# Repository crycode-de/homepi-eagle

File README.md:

# HomePi Eagle

Dieses Repository beinhaltet die Eagle-Dateien für die Hardware des HomePi Projektes.

Das gesamte HomePi Projekt wird hier beschrieben: [https://crycode.de/category/homepi](https://crycode.de/category/homepi)

**Die Verwendung erfolgt grundsätzlich auf eigenes Risiko und ohne Gewähr!**

## Lizenz

Creative Commons Attribution-NonCommercial-ShareAlike 4.0 International (CC BY-NC-SA 4.0)

Copyright (c) 2015-2024 Peter Müller <peter@crycode.de> [https://crycode.de/](https://crycode.de/)

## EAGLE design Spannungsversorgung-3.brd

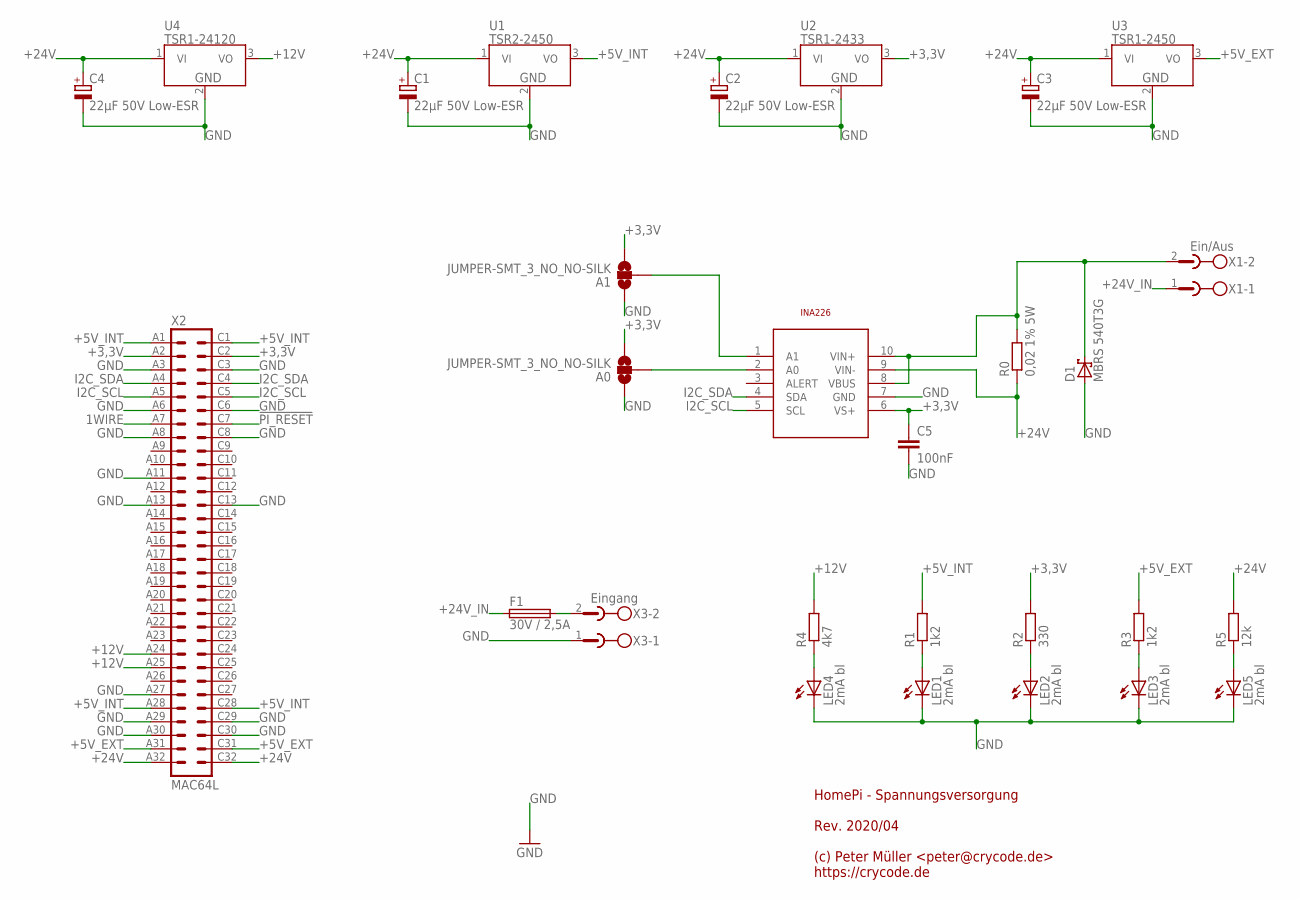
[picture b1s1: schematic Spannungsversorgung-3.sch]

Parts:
A0, A1: JUMPER-SMT_3_NO_NO-SILK; SMT-JUMPER_3_NO_NO-SILK
C1, C2, C3, C4: 22µF 50V Low-ESR; E2-5
C5: 100nF; C1206
D1: MBRS 540T3G; SMC
F1: 30V / 2,5A; LITTLEFUSE
IC1: TI-INA226
LED1, LED2, LED3, LED4, LED5: 2mA bl; CHIPLED_1206
R0: 0,02 1% 5W; R2512
R1, R3: 1k2; R1206
R2: 330; R1206
R4: 4k7; R1206
R5: 12k; R1206
U1: TSR2-2450; TSR2
U2: TSR1-2433; TSR1
U3: TSR1-2450; TSR1
U4: TSR1-24120; TSR1
X1: Ein/Aus; MSTBA2
X2: MAC64L
X3: Eingang; MSTBA2

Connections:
1WIRE: X2.A7
!PI_RESET: X2.C7
+3,3V: A0.3, A1.3, C5.1, IC1.6 (VS+), R2.2, U2.3 (VO), X2.A2, X2.C2
+5V_EXT: R3.2, U3.3 (VO), X2.A31, X2.C31
+5V_INT: R1.2, U1.3 (VO), X2.A1, X2.A28, X2.C1, X2.C28
+12V: R4.2, U4.3 (VO), X2.A24, X2.A25
+24V: C1.+, C2.+, C3.+, C4.+, IC1.9 (VIN-), R0.1, R5.2, U1.1 (VI), U2.1 (VI), U3.1 (VI), U4.1 (VI), X2.A32, X2.C32
+24V_1: D1.C, IC1.8 (VBUS), IC1.10 (VIN+), R0.2, X1.2
+24V_IN: F1.1, X1.1
+24V_IN_RAW: F1.2, X3.2
GND: A0.1, A1.1, C1.-, C2.-, C3.-, C4.-, C5.2, D1.A, IC1.7 (GND), LED1.C, LED2.C, LED3.C, LED4.C, LED5.C, U1.2 (GND), U2.2 (GND), U3.2 (GND), U4.2 (GND), X2.A3, X2.A6, X2.A8, X2.A11, X2.A13, X2.A27, X2.A29, X2.A30, X2.C3, X2.C6, X2.C8, X2.C13, X2.C29, X2.C30, X3.1
I2C_SCL: IC1.5 (SCL), X2.A5, X2.C5
I2C_SDA: IC1.4 (SDA), X2.A4, X2.C4
unnamed: A0.2, IC1.2 (A0)
unnamed: A1.2, IC1.1 (A1)
unnamed: LED5.A, R5.1
unnamed: LED1.A, R1.1
unnamed: LED2.A, R2.1
unnamed: LED3.A, R3.1
unnamed: LED4.A, R4.1

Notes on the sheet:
HomePi - Spannungsversorgung Rev. 2020/04 (c) Peter Müller <peter@crycode.de> https://crycode.de

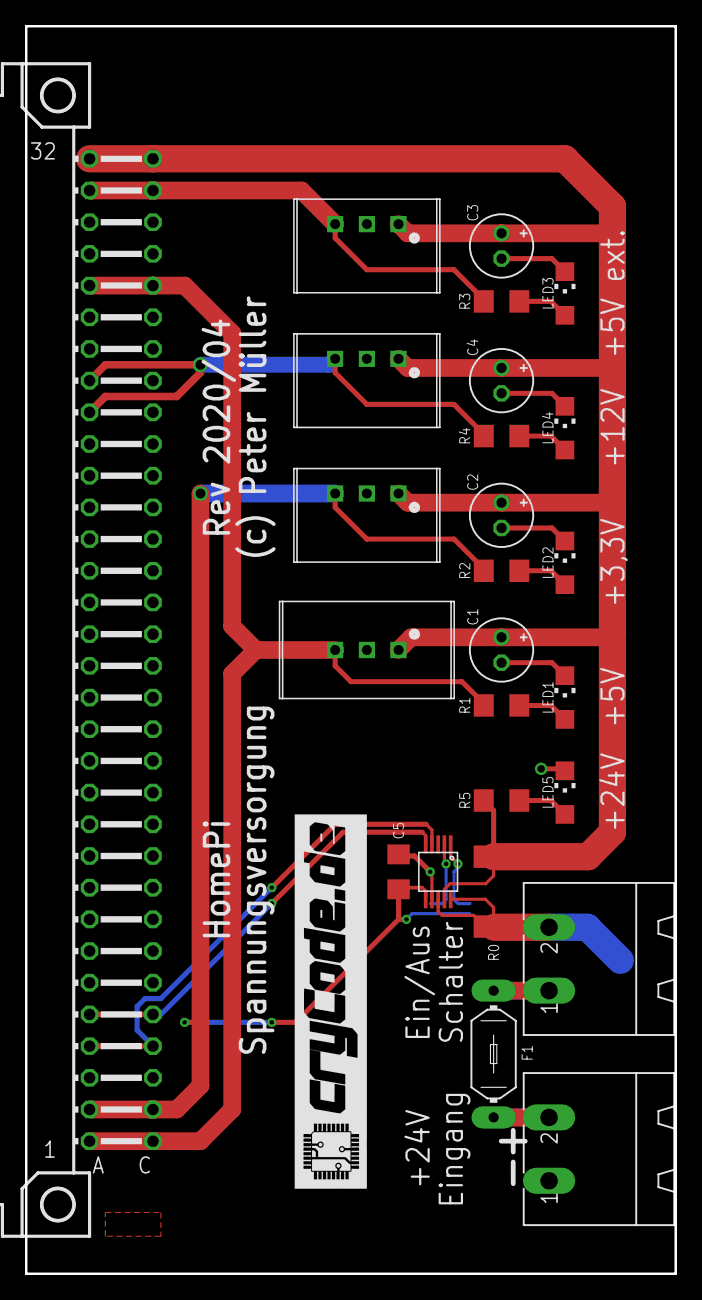
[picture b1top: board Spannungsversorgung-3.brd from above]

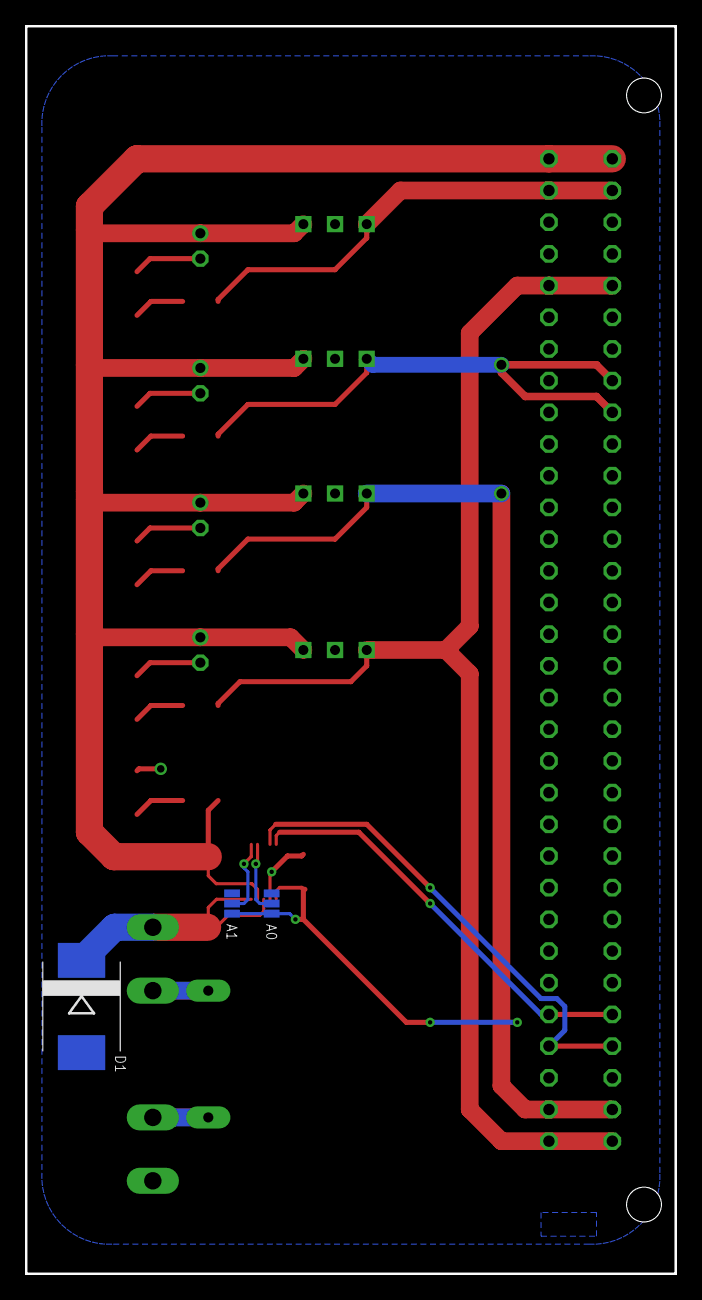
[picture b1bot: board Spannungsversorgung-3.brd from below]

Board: 2 copper layers, 52.1 x 100.0 mm, 29 parts (3 on the bottom side), 18 nets.

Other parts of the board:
U$1: 30MM

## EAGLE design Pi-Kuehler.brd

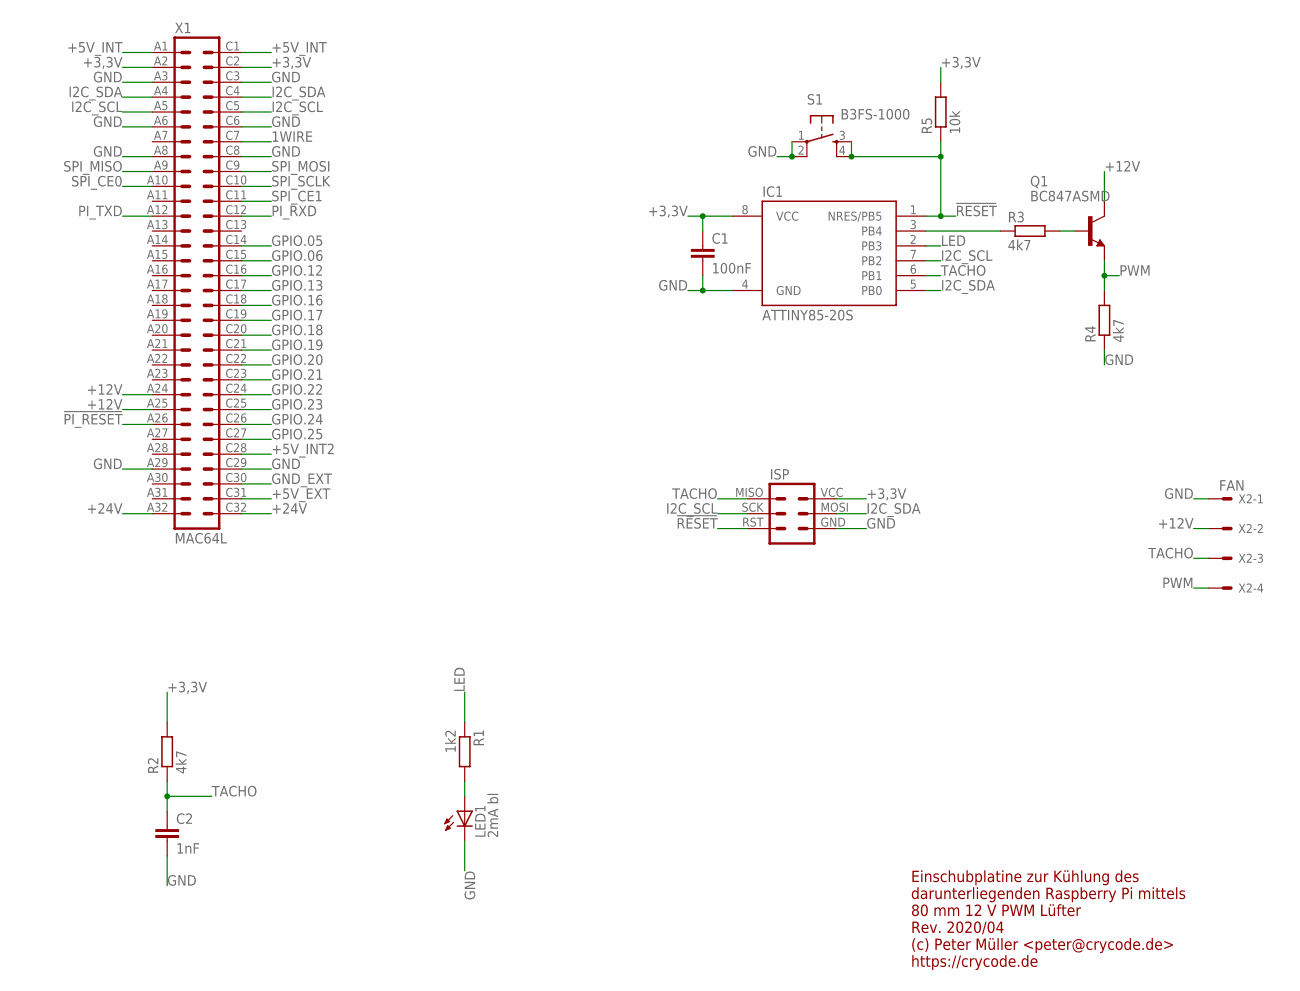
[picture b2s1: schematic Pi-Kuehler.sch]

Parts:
C1: 100nF; C1206
C2: 1nF; C1206
IC1: ATTINY85-20S; SOIC8_EIAJ_208MIL
ISP: ISPVIAS-ONLY-1.27MM; ISP-VIAS-ONLY-1.27MM
LED1: 2mA bl; CHIPLED_1206
Q1: BC847ASMD; SOT23
R1: 1k2; R1206
R2, R3, R4: 4k7; R1206
R5: 10k; R1206
S1: B3FS-1000
X1: MAC64L
X2: FAN; 6410-04

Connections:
1WIRE: X1.C7
!PI_RESET: X1.A26
!RESET: IC1.1 (NRES/PB5), ISP.RST, R5.1, S1.3 (S), S1.4 (S1)
+3,3V: C1.1, IC1.8 (VCC), ISP.VCC, R2.2, R5.2, X1.A2, X1.C2
+5V_EXT: X1.C31
+5V_INT: X1.A1, X1.C1
+5V_INT2: X1.C28
+12V: Q1.3 (C), X1.A24, X1.A25, X2.2
+24V: X1.A32, X1.C32
GND: C1.2, C2.2, IC1.4 (GND), ISP.GND, LED1.C, R4.1, S1.1, S1.2 (P1), X1.A3, X1.A6, X1.A8, X1.A29, X1.C3, X1.C6, X1.C8, X1.C29, X2.1
GND_EXT: X1.C30
GPIO.05: X1.C14
GPIO.06: X1.C15
GPIO.12: X1.C16
GPIO.13: X1.C17
GPIO.16: X1.C18
GPIO.17: X1.C19
GPIO.18: X1.C20
GPIO.19: X1.C21
GPIO.20: X1.C22
GPIO.21: X1.C23
GPIO.22: X1.C24
GPIO.23: X1.C25
GPIO.24: X1.C26
GPIO.25: X1.C27
I2C_SCL: IC1.7 (PB2), ISP.SCK, X1.A5, X1.C5
I2C_SDA: IC1.5 (PB0), ISP.MOSI, X1.A4, X1.C4
LED: IC1.2 (PB3), R1.1
unnamed: IC1.3 (PB4), R3.1
unnamed: Q1.1 (B), R3.2
unnamed: LED1.A, R1.2
PI_RXD: X1.C12
PI_TXD: X1.A12
PWM: Q1.2 (E), R4.2, X2.4
SPI_CE0: X1.A10
SPI_CE1: X1.C11
SPI_MISO: X1.A9
SPI_MOSI: X1.C9
SPI_SCLK: X1.C10
TACHO: C2.1, IC1.6 (PB1), ISP.MISO, R2.1, X2.3

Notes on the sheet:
Einschubplatine zur Kühlung des darunterliegenden Raspberry Pi mittels 80 mm 12 V PWM Lüfter Rev. 2020/04 (c) Peter Müller <peter@crycode.de> https://crycode.de

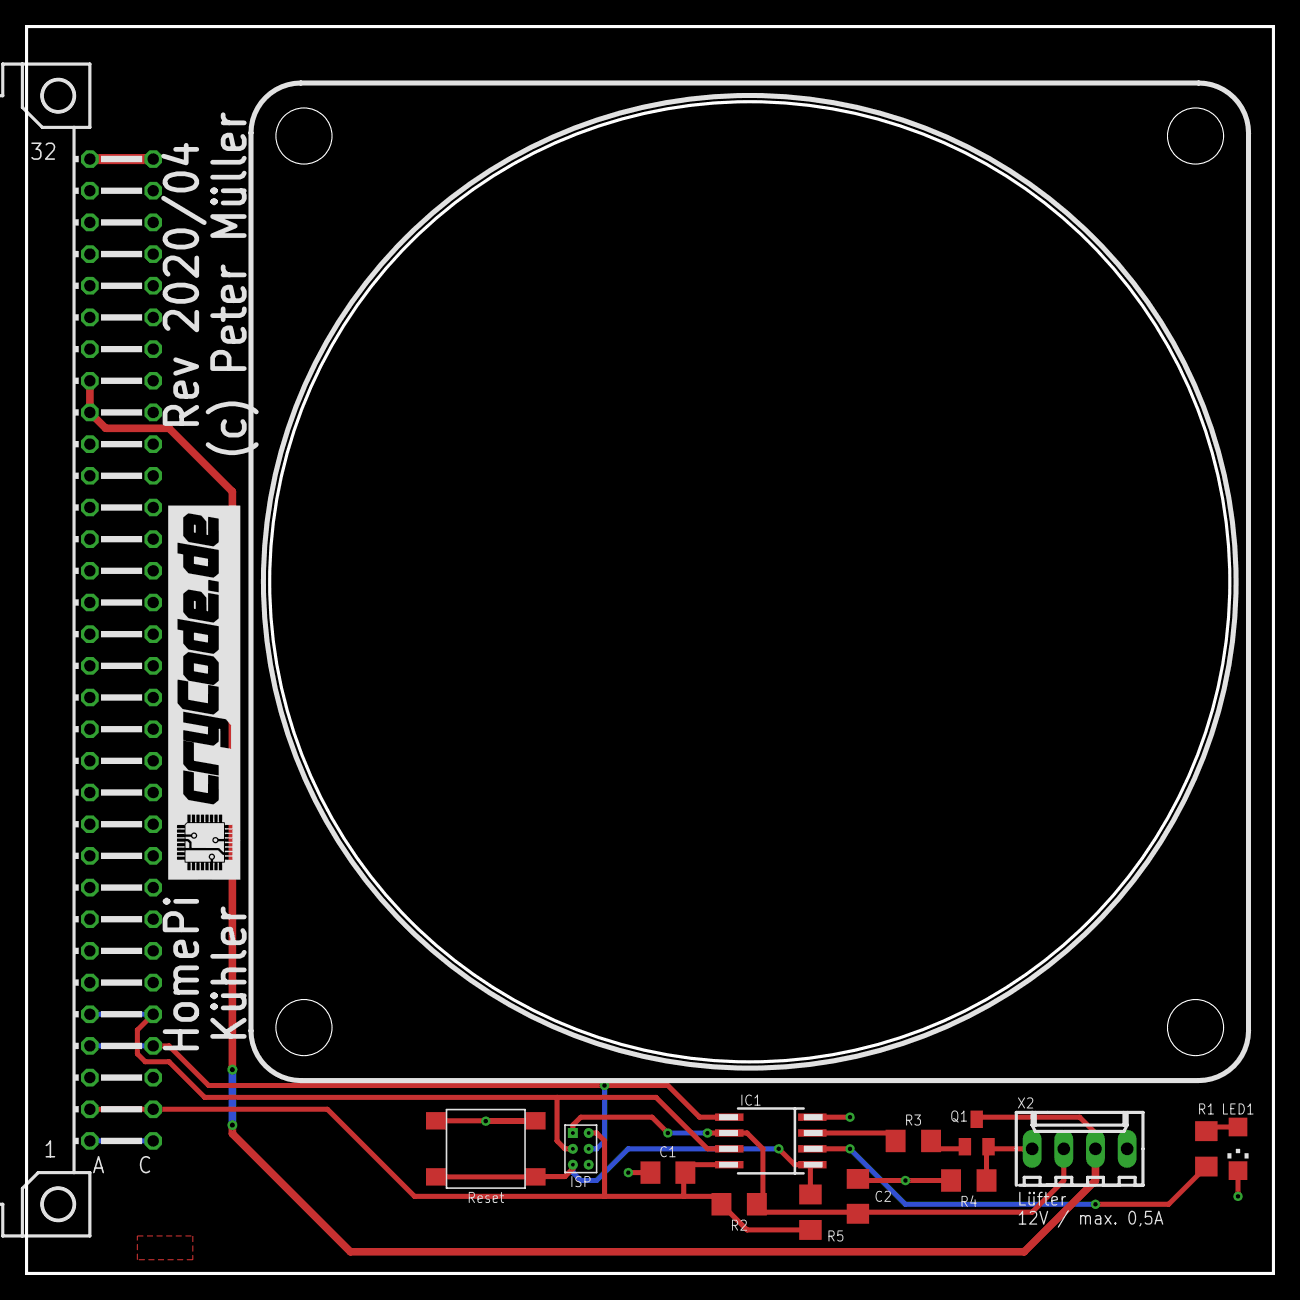
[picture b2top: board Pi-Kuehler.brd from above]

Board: 2 copper layers, 100.0 x 100.0 mm, 16 parts (0 on the bottom side), 14 nets.

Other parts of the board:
U$1: 30MM
U$2: 80MM

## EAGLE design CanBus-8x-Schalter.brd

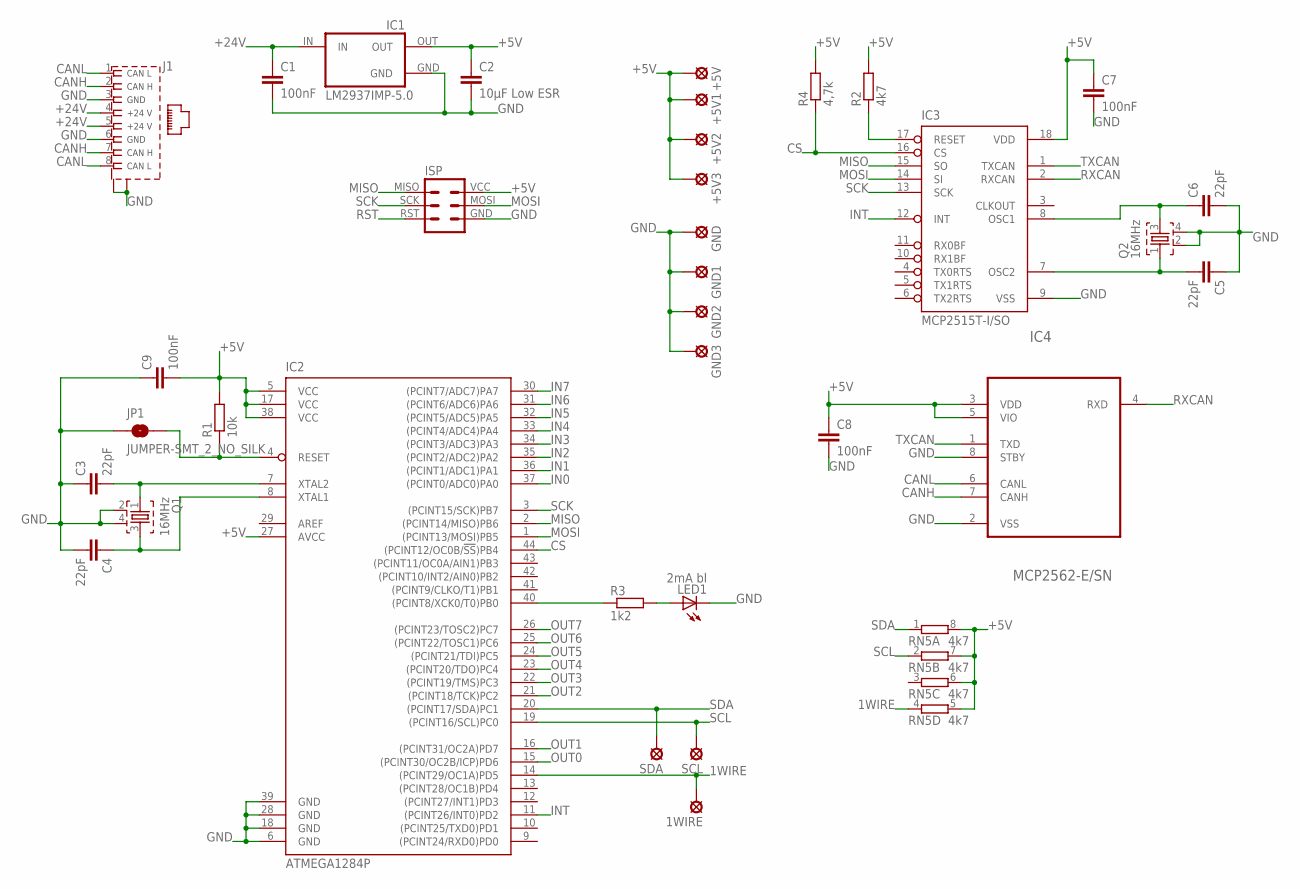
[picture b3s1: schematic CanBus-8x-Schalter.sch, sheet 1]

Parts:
1WIRE: LSP13
+5V, +5V1, +5V2, +5V3: LSP13
C1, C7, C8, C9: 100nF; C0805
C2: 10µF Low ESR; C0805
C3, C4, C5, C6: 22pF; C0805
GND, GND1, GND2, GND3: LSP13
IC1: LM2937IMP-5.0; SOT223
IC2: ATMEGA1284P; TQFP44
IC3: MCP2515T-I/SO; SO18L
IC4: MCP2562-E/SN; SO08
ISP: ISPVIAS-ONLY-1.27MM; ISP-VIAS-ONLY-1.27MM
J1: RJ45-CAN; MEBP_8-8G
JP1: JUMPER-SMT_2_NO_SILK; SMT-JUMPER_2_NO_SILK
LED1: 2mA bl; CHIPLED_1206
Q1, Q2: 16MHz; MJ-5X3.2
R1: 10k; R0805
R2: 4k7; R0805
R3: 1k2; R0805
R4: 4,7k; R0805
RN5: 4k7; 0603-ARC
SCL: LSP13
SDA: LSP13

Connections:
1WIRE: 1WIRE.MP, IC2.14 ((PCINT29/OC1A)PD5), RN5.4 (1)
+5V: +5V.MP, +5V1.MP, +5V2.MP, +5V3.MP, C2.1, C7.1, C8.1, C9.2, IC1.OUT, IC2.5 (VCC), IC2.17 (VCC), IC2.27 (AVCC), IC2.38 (VCC), IC3.18 (VDD), IC4.3 (VDD), IC4.5 (VIO), ISP.VCC, R1.2, R2.2, R4.2, RN5.5 (2), RN5.6 (2), RN5.7 (2), RN5.8 (2); also elsewhere on the board
+24V: C1.1, IC1.IN, J1.4, J1.5; also elsewhere on the board
CANH: IC4.7 (CANH), J1.2, J1.7
CANL: IC4.6 (CANL), J1.1, J1.8
CS: IC2.44 ((PCINT12/OC0B/!SS!)PB4), IC3.16 (CS), R4.1
GND: C1.2, C2.2, C3.1, C4.2, C5.1, C6.2, C7.2, C8.2, C9.1, GND.MP, GND1.MP, GND2.MP, GND3.MP, IC1.GND, IC1.GND@ (GND), IC2.6 (GND), IC2.18 (GND), IC2.28 (GND), IC2.39 (GND), IC3.9 (VSS), IC4.2 (VSS), IC4.8 (STBY), ISP.GND, J1.3, J1.6, J1.G1 (S1), J1.G2 (S2), JP1.1, LED1.C, Q1.2, Q1.4, Q2.2, Q2.4; also elsewhere on the board
IN0: IC2.37 ((PCINT0/ADC0)PA0); also elsewhere on the board
IN1: IC2.36 ((PCINT1/ADC1)PA1); also elsewhere on the board
IN2: IC2.35 ((PCINT2/ADC2)PA2); also elsewhere on the board
IN3: IC2.34 ((PCINT3/ADC3)PA3); also elsewhere on the board
IN4: IC2.33 ((PCINT4/ADC4)PA4); also elsewhere on the board
IN5: IC2.32 ((PCINT5/ADC5)PA5); also elsewhere on the board
IN6: IC2.31 ((PCINT6/ADC6)PA6); also elsewhere on the board
IN7: IC2.30 ((PCINT7/ADC7)PA7); also elsewhere on the board
INT: IC2.11 ((PCINT26/INT0)PD2), IC3.12 (INT)
MISO: IC2.2 ((PCINT14/MISO)PB6), IC3.15 (SO), ISP.MISO
MOSI: IC2.1 ((PCINT13/MOSI)PB5), IC3.14 (SI), ISP.MOSI
unnamed: IC3.17 (RESET), R2.1
unnamed: IC2.40 ((PCINT8/XCK0/T0)PB0), R3.1
unnamed: LED1.A, R3.2
OUT0: IC2.15 ((PCINT30/OC2B/ICP)PD6); also elsewhere on the board
OUT1: IC2.16 ((PCINT31/OC2A)PD7); also elsewhere on the board
OUT2: IC2.21 ((PCINT18/TCK)PC2); also elsewhere on the board
OUT3: IC2.22 ((PCINT19/TMS)PC3); also elsewhere on the board
OUT4: IC2.23 ((PCINT20/TDO)PC4); also elsewhere on the board
OUT5: IC2.24 ((PCINT21/TDI)PC5); also elsewhere on the board
OUT6: IC2.25 ((PCINT22/TOSC1)PC6); also elsewhere on the board
OUT7: IC2.26 ((PCINT23/TOSC2)PC7); also elsewhere on the board
RST: IC2.4 (RESET), ISP.RST, JP1.2, R1.1
RXCAN: IC3.2 (RXCAN), IC4.4 (RXD)
SCK: IC2.3 ((PCINT15/SCK)PB7), IC3.13 (SCK), ISP.SCK
SCL: IC2.19 ((PCINT16/SCL)PC0), RN5.2 (1), SCL.MP
SDA: IC2.20 ((PCINT17/SDA)PC1), RN5.1, SDA.MP
TXCAN: IC3.1 (TXCAN), IC4.1 (TXD)
XTAL1: C3.2, IC2.7 (XTAL2), Q1.1
XTAL2: C4.1, IC2.8 (XTAL1), Q1.3
XTAL3: C5.2, IC3.7 (OSC2), Q2.1
XTAL4: C6.1, IC3.8 (OSC1), Q2.3

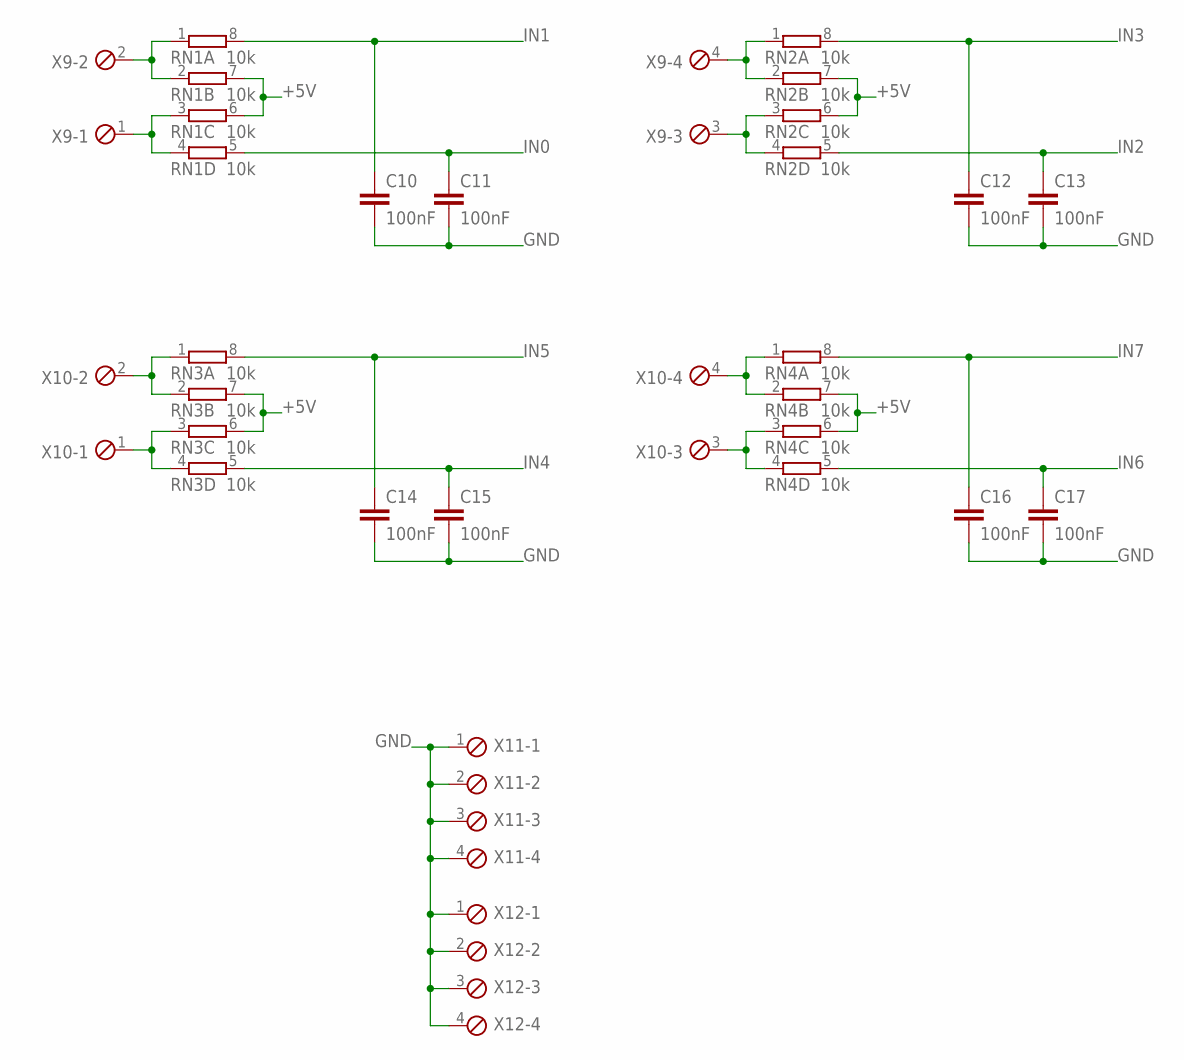
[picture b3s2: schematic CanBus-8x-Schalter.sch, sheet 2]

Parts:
C10, C11, C12, C13, C14, C15, C16, C17: 100nF; C0805
RN1, RN2, RN3, RN4: 10k; 0603-ARC
X9, X10, X11, X12: MPT4; 4POL254

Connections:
+5V: RN1.6 (2), RN1.7 (2), RN2.6 (2), RN2.7 (2), RN3.6 (2), RN3.7 (2), RN4.6 (2), RN4.7 (2); also elsewhere on the board
GND: C10.2, C11.2, C12.2, C13.2, C14.2, C15.2, C16.2, C17.2, X11.1, X11.2, X11.3, X11.4, X12.1, X12.2, X12.3, X12.4; also elsewhere on the board
IN0: C11.1, RN1.5 (2); also elsewhere on the board
IN1: C10.1, RN1.8 (2); also elsewhere on the board
IN2: C13.1, RN2.5 (2); also elsewhere on the board
IN3: C12.1, RN2.8 (2); also elsewhere on the board
IN4: C15.1, RN3.5 (2); also elsewhere on the board
IN5: C14.1, RN3.8 (2); also elsewhere on the board
IN6: C17.1, RN4.5 (2); also elsewhere on the board
IN7: C16.1, RN4.8 (2); also elsewhere on the board
unnamed: RN3.3 (1), RN3.4 (1), X10.1
unnamed: RN3.1, RN3.2 (1), X10.2
unnamed: RN1.3 (1), RN1.4 (1), X9.1
unnamed: RN1.1, RN1.2 (1), X9.2
unnamed: RN4.3 (1), RN4.4 (1), X10.3
unnamed: RN4.1, RN4.2 (1), X10.4
unnamed: RN2.3 (1), RN2.4 (1), X9.3
unnamed: RN2.1, RN2.2 (1), X9.4

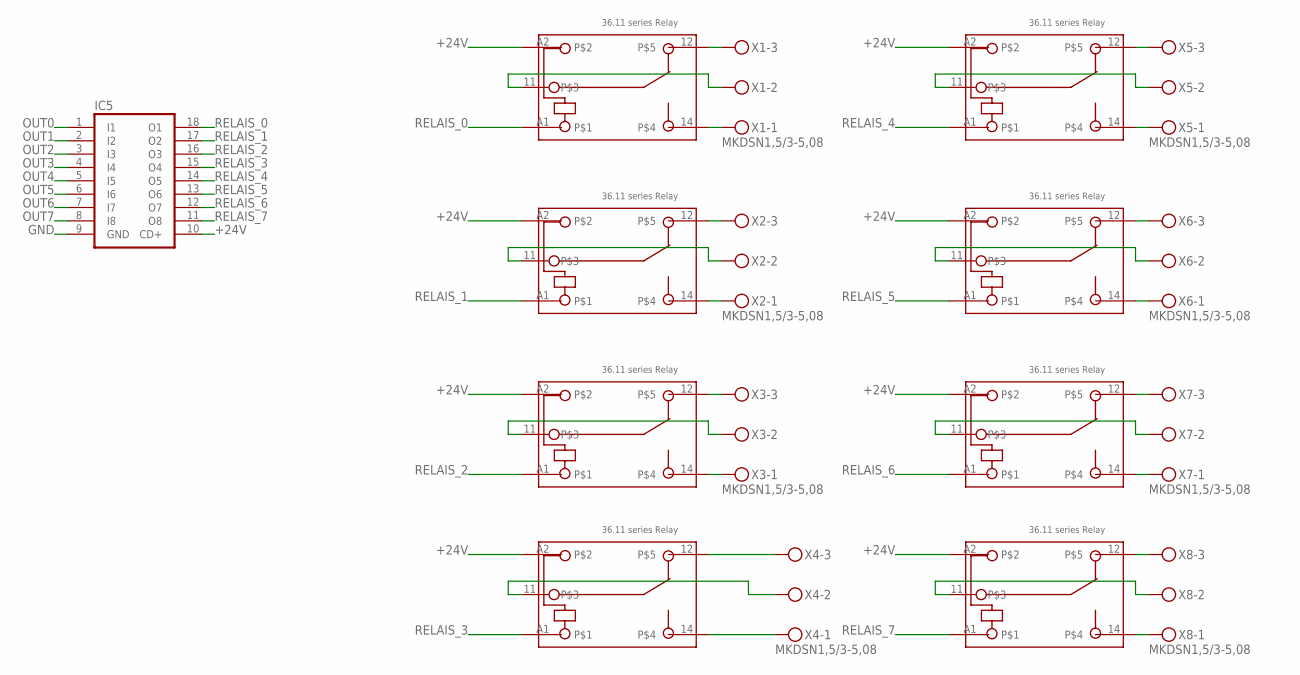
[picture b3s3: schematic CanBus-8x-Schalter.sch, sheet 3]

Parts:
IC5: ULN2803A-SO18W; SO18W
K1, K2, K3, K4, K5, K6, K7, K8: 36.11
X1, X2, X3, X4, X5, X6, X7, X8: MKDSN1,5/3-5,08

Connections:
+24V: IC5.10 (CD+), K1.A2, K2.A2, K3.A2, K4.A2, K5.A2, K6.A2, K7.A2, K8.A2; also elsewhere on the board
GND: IC5.9 (GND); also elsewhere on the board
unnamed: K2.12, X2.3
unnamed: K2.14, X2.1
unnamed: K2.11, X2.2
unnamed: K1.12, X1.3
unnamed: K1.14, X1.1
unnamed: K1.11, X1.2
unnamed: K3.12, X3.3
unnamed: K3.14, X3.1
unnamed: K3.11, X3.2
unnamed: K4.12, X4.3
unnamed: K4.14, X4.1
unnamed: K4.11, X4.2
unnamed: K6.12, X6.3
unnamed: K6.14, X6.1
unnamed: K6.11, X6.2
unnamed: K5.12, X5.3
unnamed: K5.14, X5.1
unnamed: K5.11, X5.2
unnamed: K7.12, X7.3
unnamed: K7.14, X7.1
unnamed: K7.11, X7.2
unnamed: K8.12, X8.3
unnamed: K8.14, X8.1
unnamed: K8.11, X8.2
OUT0: IC5.1 (I1); also elsewhere on the board
OUT1: IC5.2 (I2); also elsewhere on the board
OUT2: IC5.3 (I3); also elsewhere on the board
OUT3: IC5.4 (I4); also elsewhere on the board
OUT4: IC5.5 (I5); also elsewhere on the board
OUT5: IC5.6 (I6); also elsewhere on the board
OUT6: IC5.7 (I7); also elsewhere on the board
OUT7: IC5.8 (I8); also elsewhere on the board
RELAIS_0: IC5.18 (O1), K1.A1
RELAIS_1: IC5.17 (O2), K2.A1
RELAIS_2: IC5.16 (O3), K3.A1
RELAIS_3: IC5.15 (O4), K4.A1
RELAIS_4: IC5.14 (O5), K5.A1
RELAIS_5: IC5.13 (O6), K6.A1
RELAIS_6: IC5.12 (O7), K7.A1
RELAIS_7: IC5.11 (O8), K8.A1

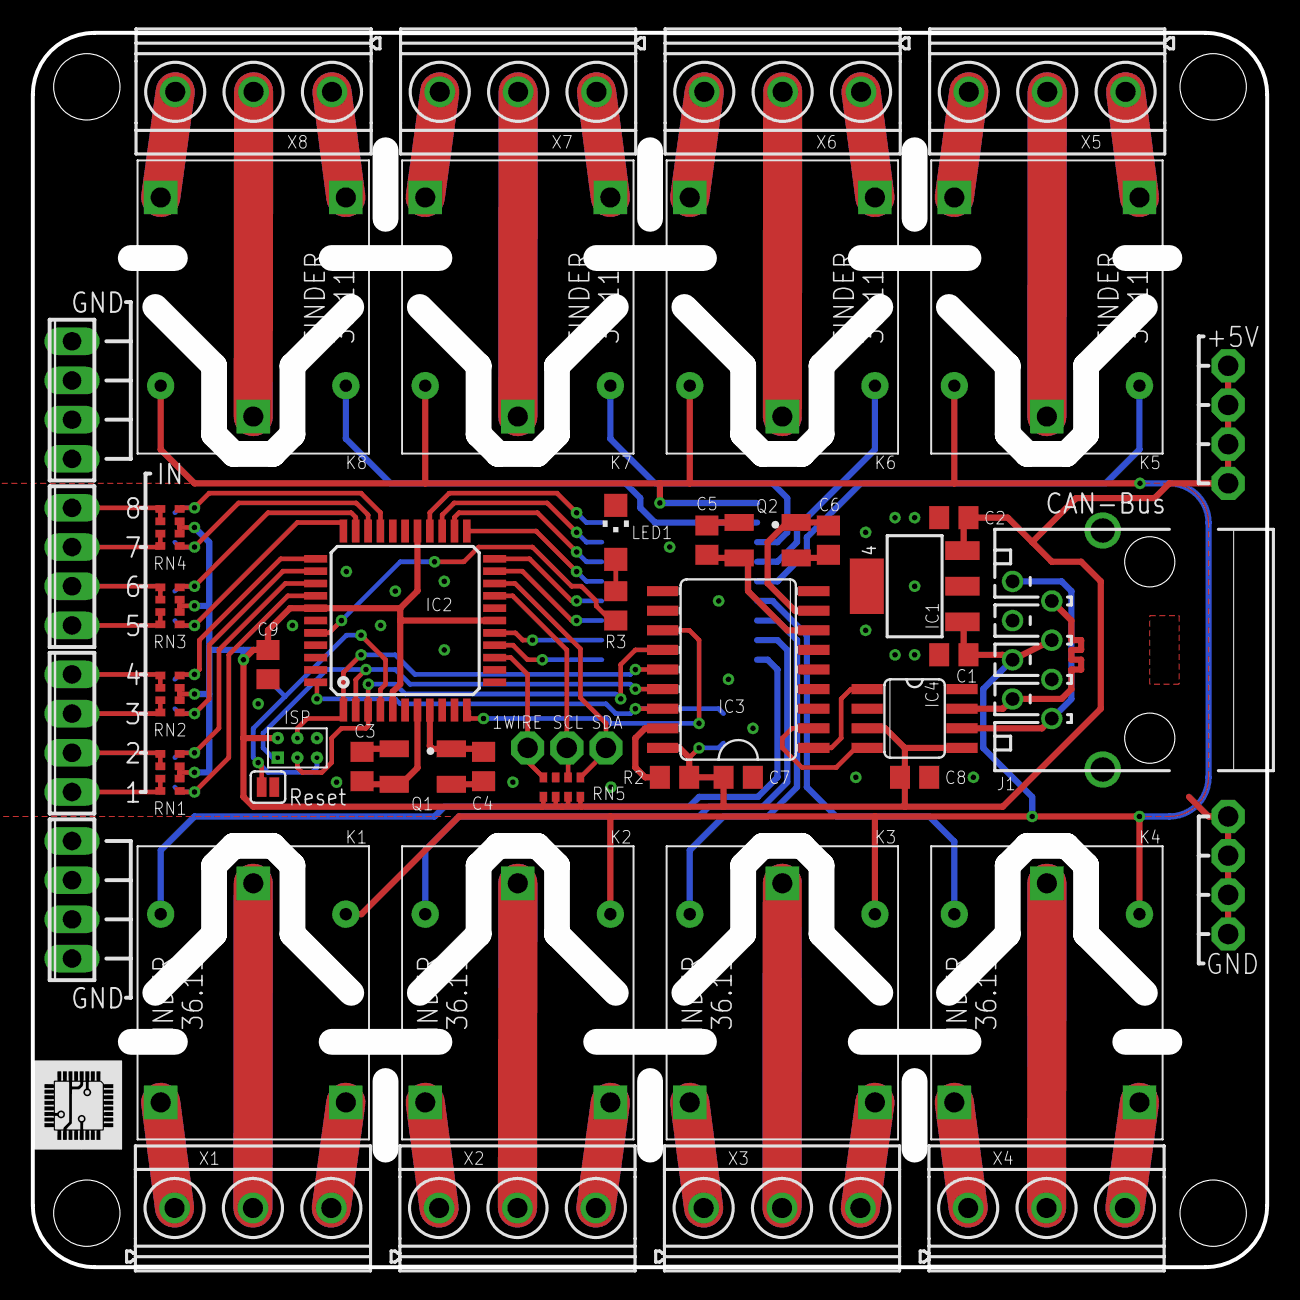
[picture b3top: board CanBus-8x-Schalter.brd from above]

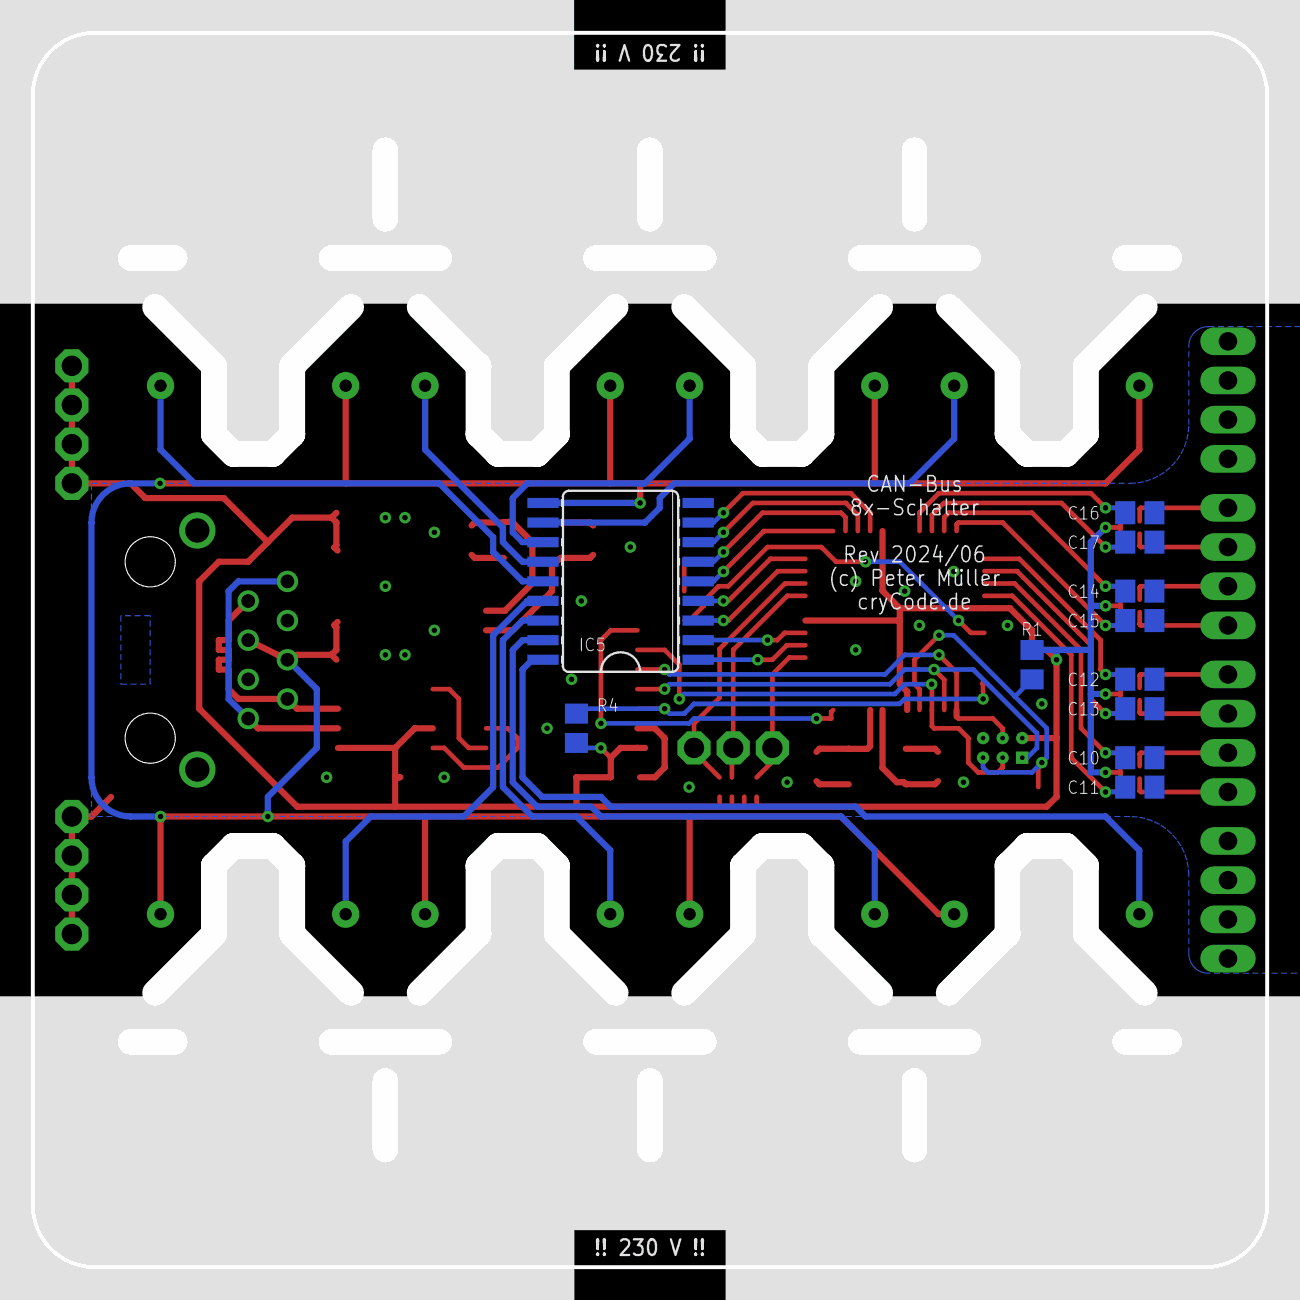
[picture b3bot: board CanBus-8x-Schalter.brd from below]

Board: 2 copper layers, 80.0 x 80.0 mm, 69 parts (11 on the bottom side), 79 nets.

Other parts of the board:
U$1: 30MM_LOGO

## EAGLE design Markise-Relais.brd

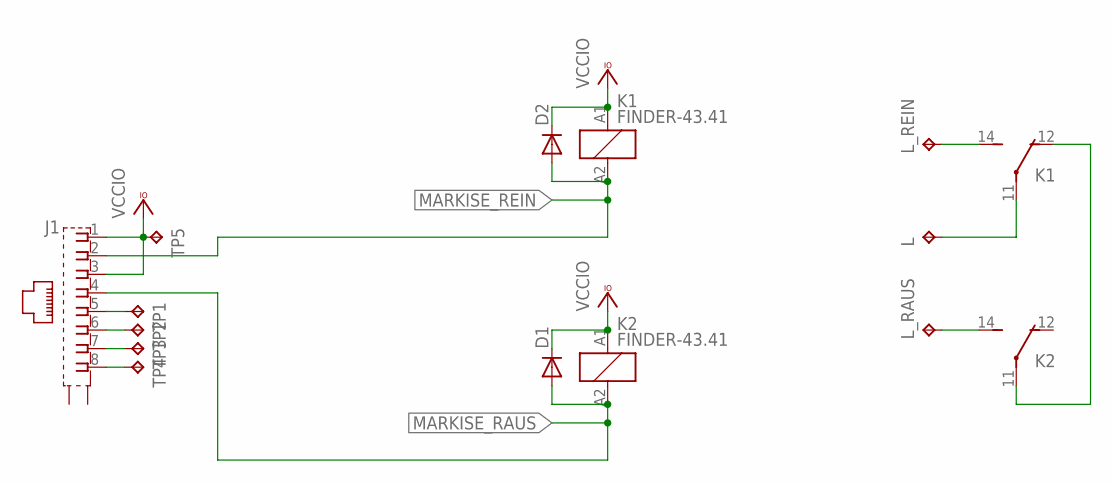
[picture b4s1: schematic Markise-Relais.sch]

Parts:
D1, D2: DIODE-D-7.5; D-7.5
J1: 555141-1; 555153-1
K1, K2: FINDER-43.41
L: TPPAD1-20Y; P1-20Y
L_RAUS: TPPAD1-20Y; P1-20Y
L_REIN: TPPAD1-20Y; P1-20Y
TP1, TP2, TP3, TP4, TP5: TPPAD1-13; P1-13

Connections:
MARKISE_RAUS: D1.A, J1.4, K2.A2 (2)
MARKISE_REIN: D2.A, J1.2, K1.A2 (2)
unnamed: K1.11, L.TP
unnamed: K1.14 (S), L_REIN.TP
unnamed: K1.12 (O), K2.11
unnamed: K2.14 (S), L_RAUS.TP
unnamed: J1.5, TP1.TP
unnamed: J1.6, TP2.TP
unnamed: J1.7, TP3.TP
unnamed: J1.8, TP4.TP
VCCIO: D1.C, D2.C, J1.1, J1.3, K1.A1 (1), K2.A1 (1), TP5.TP

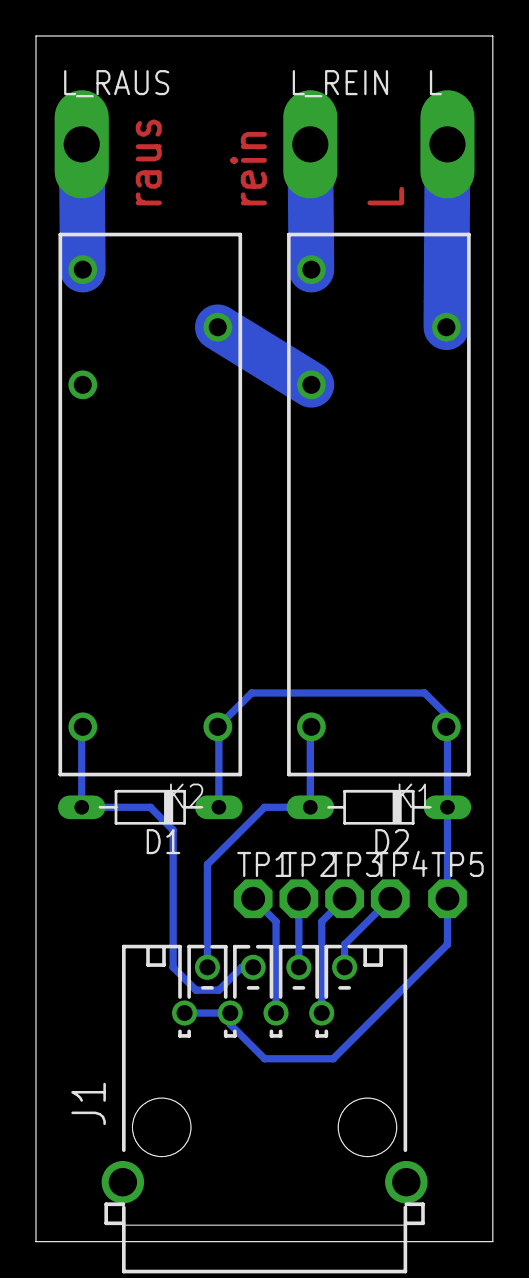
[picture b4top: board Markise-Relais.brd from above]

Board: 2 copper layers, 25.4 x 67.0 mm, 13 parts (0 on the bottom side), 11 nets.

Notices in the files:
CAN-Shield.brd:
(C) 2020 Peter Müller
parts and their libraries:
pogo-isp: Copyright (c) 2020 Peter Müller
SparkFun-Jumpers: Licensing: Creative Commons ShareAlike 4.0 International - https://creativecommons.org/licenses/by-sa/4.0
FaBo-Sensor: Released under the Creative Commons Attribution-ShareAlike 4.0 License
https://creativecommons.org/licenses/by-sa/4.0
